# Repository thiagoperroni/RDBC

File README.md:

# RDBC
Radar Didático de Baixo Custo

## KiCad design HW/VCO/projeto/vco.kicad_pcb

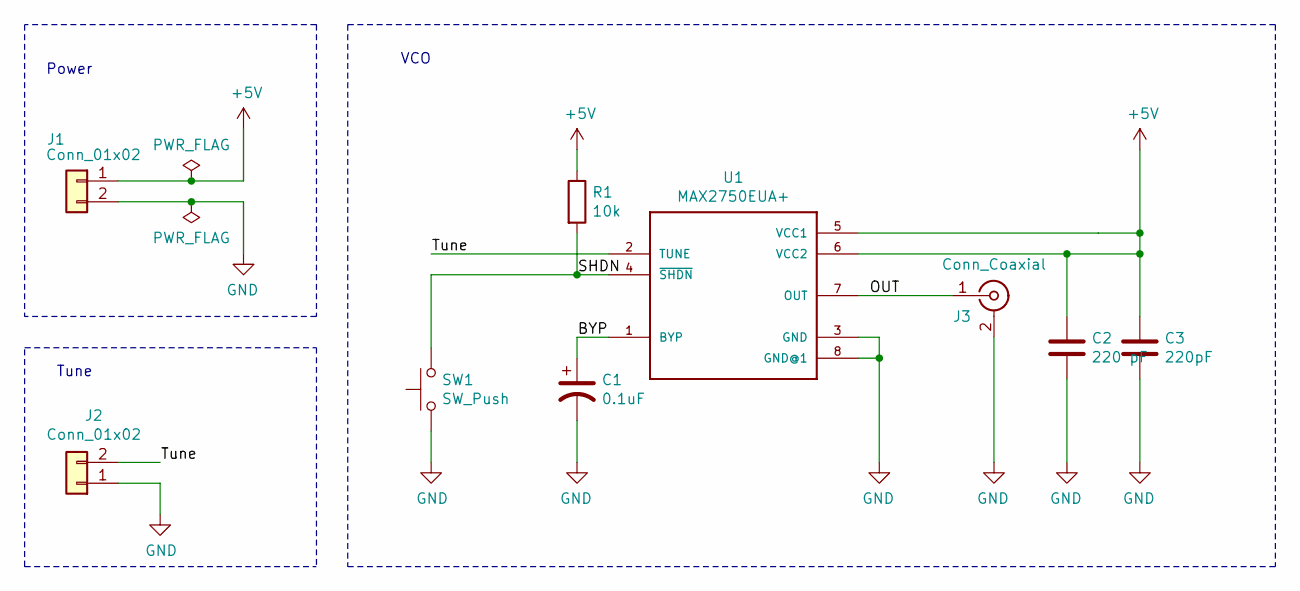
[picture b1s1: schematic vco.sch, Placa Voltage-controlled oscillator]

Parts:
C1: 0.1uF; C_0603_1608Metric
C2: 220 pF; C_0805_2012Metric
C3: 220pF; C_0805_2012Metric
J1, J2: Conn_01x02; PhoenixContact_MSTBVA_2,5_2-G-5,08_1x02_P5.08mm_Vertical
J3: Conn_Coaxial; SMA_Amphenol_901-9215_EdgeMount
R1: 10k; R_1206_3216Metric
SW1: SW_Push; switchRadar
U1: MAX2750EUA+; SOP65P490X110-8N

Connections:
+5V: C2.1, C3.1, J1.1, R1.1, U1.5 (VCC1), U1.6 (VCC2)
/BYP: C1.1, U1.1 (BYP)
/OUT: J3.1 (In), U1.7 (OUT)
/SHDN: R1.2, SW1.2, U1.4 (~SHDN~)
/Tune: J2.2, U1.2 (TUNE)
GND: C1.2, C2.2, C3.2, J1.2, J2.1, J3.2 (Ext), SW1.1, U1.3 (GND), U1.8 (GND@1)

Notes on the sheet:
Power
Tune
VCO

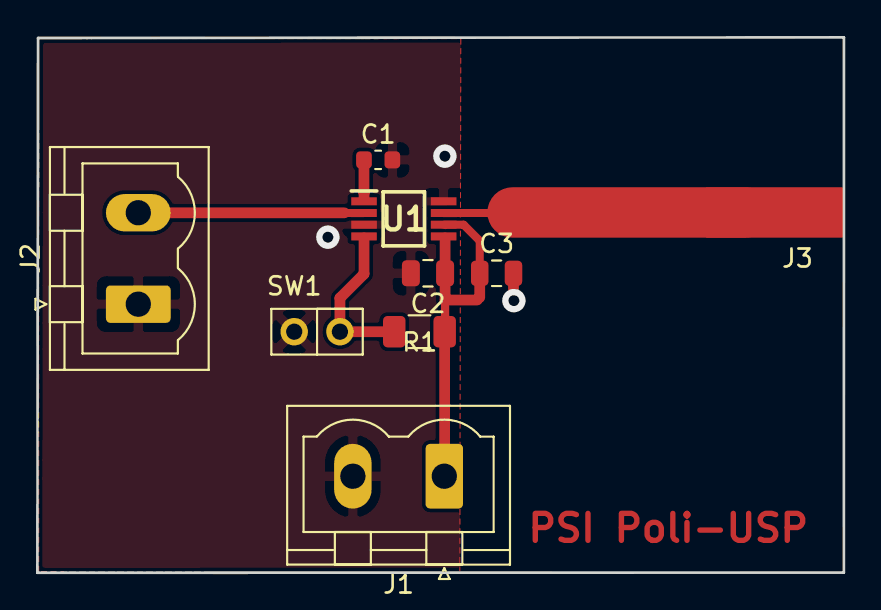
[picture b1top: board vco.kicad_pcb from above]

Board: 2 copper layers, 44.8 x 29.7 mm, 9 parts (0 on the bottom side), 6 nets.

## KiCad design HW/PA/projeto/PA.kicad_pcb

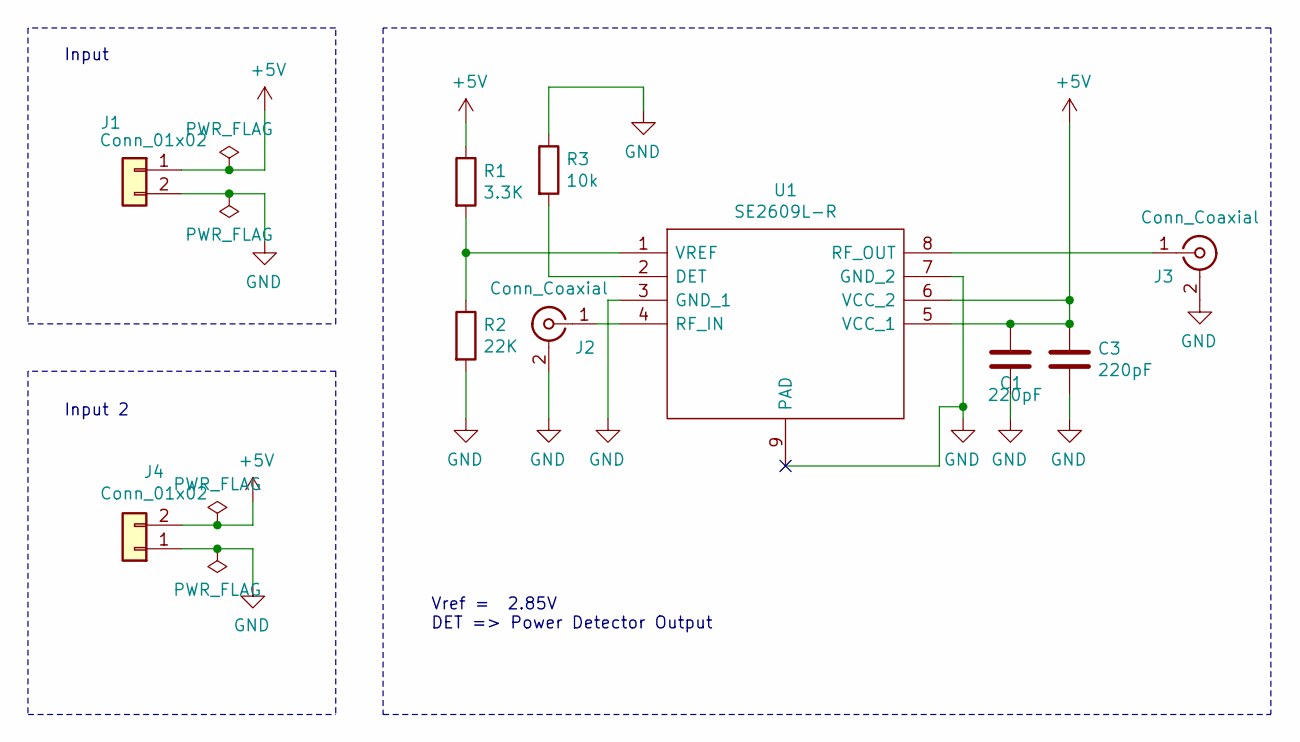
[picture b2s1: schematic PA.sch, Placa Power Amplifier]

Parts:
C1, C3: 220pF; C_0805_2012Metric
J1, J4: Conn_01x02; PhoenixContact_MSTBVA_2,5_2-G-5,08_1x02_P5.08mm_Vertical
J2, J3: Conn_Coaxial; SMA_Amphenol_901-9215_EdgeMount
R1: 3.3K; R_1206_3216Metric
R2: 22K; R_1206_3216Metric
R3: 10k; R_1206_3216Metric
U1: SE2609L-R; QFN-8; Manufacturer_Part_Number SE2609L-R

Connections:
+5V: C1.1, C3.1, J1.1, J4.2, R1.1, U1.5 (VCC_1), U1.6 (VCC_2)
GND: C1.2, C3.2, J1.2, J2.2 (Ext), J3.2 (Ext), J4.1, R2.2, R3.1, U1.3 (GND_1), U1.7 (GND_2), U1.9 (PAD)
unnamed: J2.1 (In), U1.4 (RF_IN)
unnamed: J3.1 (In), U1.8 (RF_OUT)
unnamed: R1.2, R2.1, U1.1 (VREF)
unnamed: R3.2, U1.2 (DET)

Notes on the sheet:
Input
Vref = 2.85V DET => Power Detector Output
Input 2

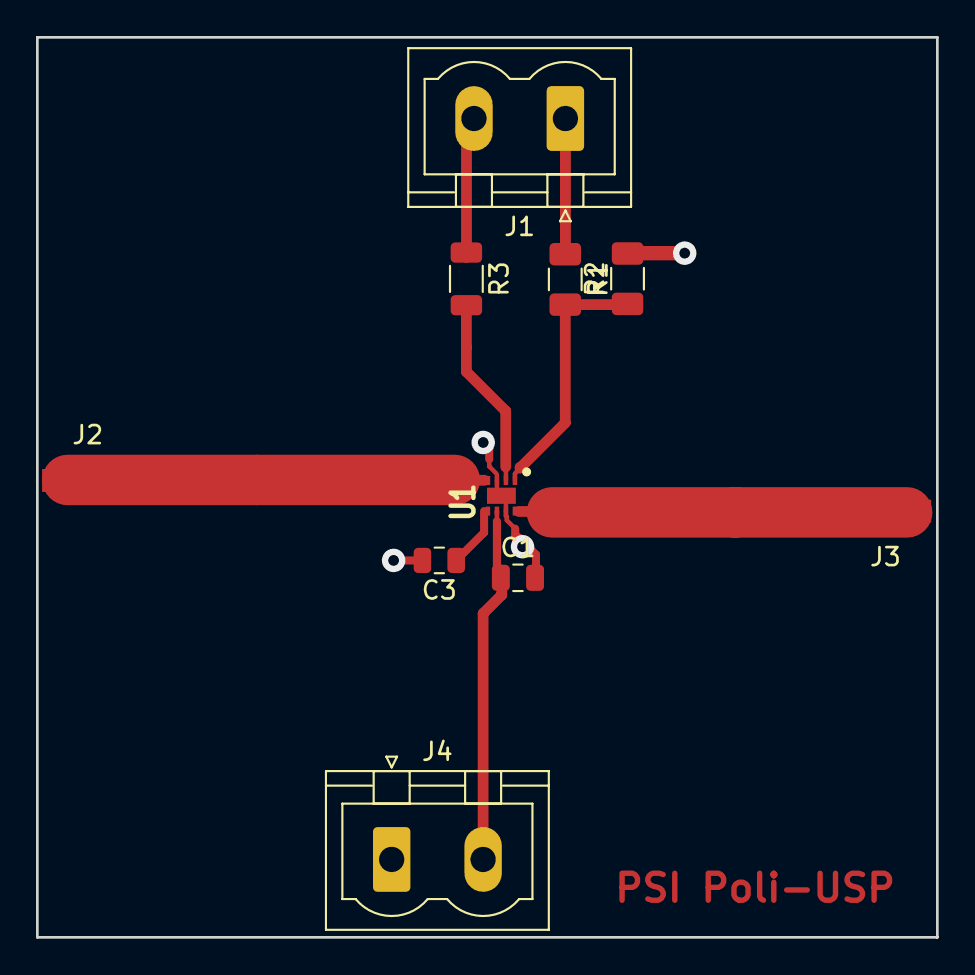
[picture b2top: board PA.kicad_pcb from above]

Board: 2 copper layers, 50.0 x 50.0 mm, 10 parts (0 on the bottom side), 6 nets.

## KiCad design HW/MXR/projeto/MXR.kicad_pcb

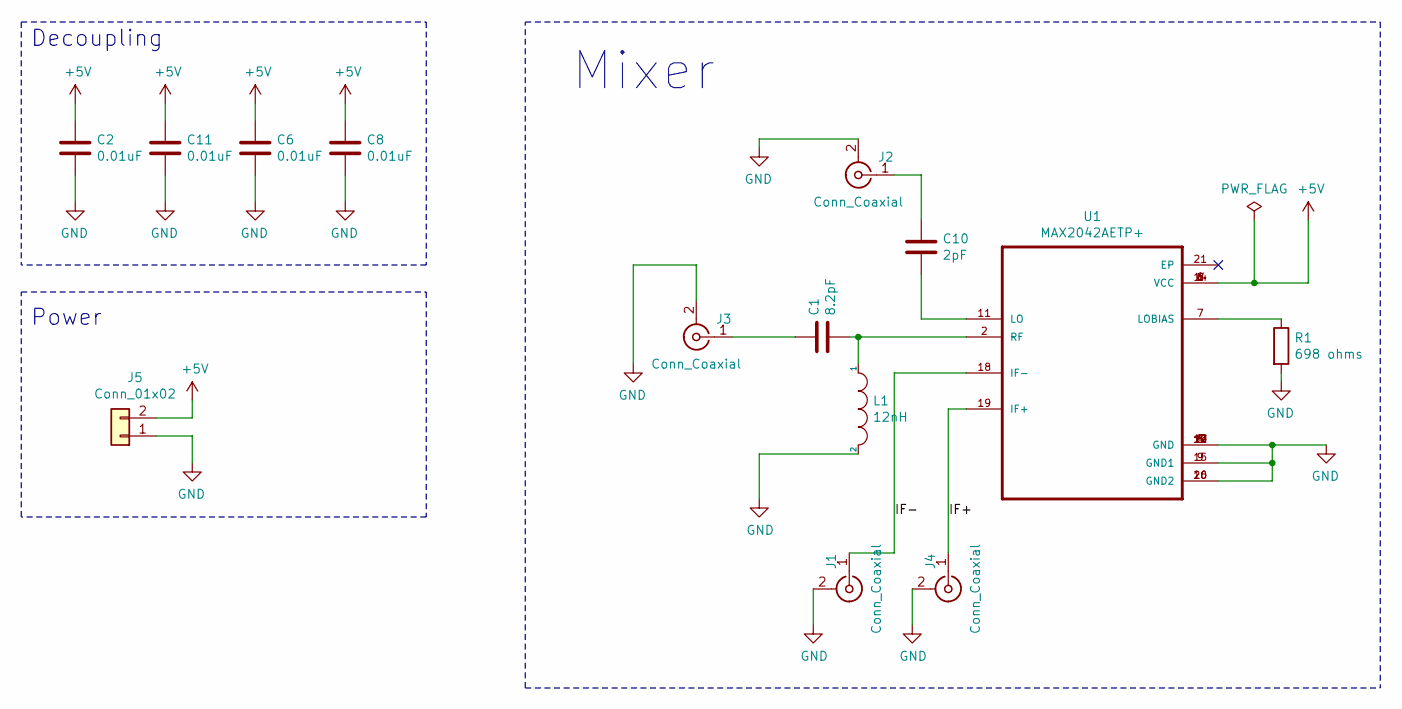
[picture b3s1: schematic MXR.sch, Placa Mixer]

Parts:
C1: 8.2pF; C_0402_1005Metric
C2, C6, C8, C11: 0.01uF; C_0402_1005Metric
C10: 2pF; CAPC1005X55N
J1, J4: Conn_Coaxial; BNC_TEConnectivity_1478204_Vertical
J2, J3: Conn_Coaxial; SMA_Amphenol_901-9215_EdgeMount
J5: Conn_01x02; PhoenixContact_MSTBVA_2,5_2-G-5,08_1x02_P5.08mm_Vertical
L1: 12nH; L_0402_1005Metric
R1: 698 ohms; R_0402_1005Metric
U1: MAX2042AETP+; TQFN-20-1EP_5x5mm_P0.65mm_EP3.1x3.1mm

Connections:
+5V: C2.1, C6.1, C8.1, C11.1, J5.2, U1.1 (VCC), U1.6 (VCC), U1.8 (VCC), U1.14 (VCC)
/IF+: J4.1 (In), U1.19 (IF+)
/IF-: J1.1 (In), U1.18 (IF-)
GND: C2.2, C6.2, C8.2, C11.2, J1.2 (Ext), J2.2 (Ext), J3.2 (Ext), J4.2 (Ext), J5.1, L1.2, R1.2, U1.3 (GND), U1.4 (GND), U1.5 (GND), U1.9 (GND1), U1.10 (GND), U1.12 (GND), U1.13 (GND), U1.15 (GND1), U1.16 (GND2), U1.17 (GND), U1.20 (GND2)
unnamed: C1.1, J3.1 (In)
unnamed: C1.2, L1.1, U1.2 (RF)
unnamed: C10.1, J2.1 (In)
unnamed: C10.2, U1.11 (LO)
unnamed: R1.1, U1.7 (LOBIAS)

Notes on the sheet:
Mixer
Decoupling
Power

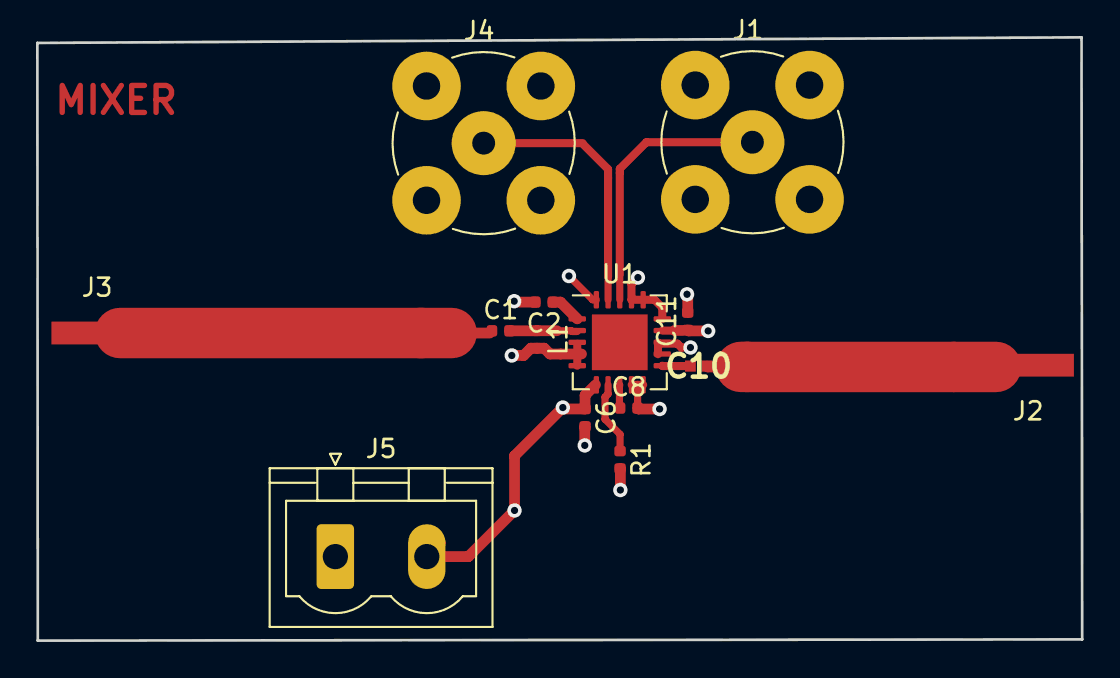
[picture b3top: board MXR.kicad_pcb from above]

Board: 2 copper layers, 58.0 x 33.5 mm, 14 parts (0 on the bottom side), 9 nets.

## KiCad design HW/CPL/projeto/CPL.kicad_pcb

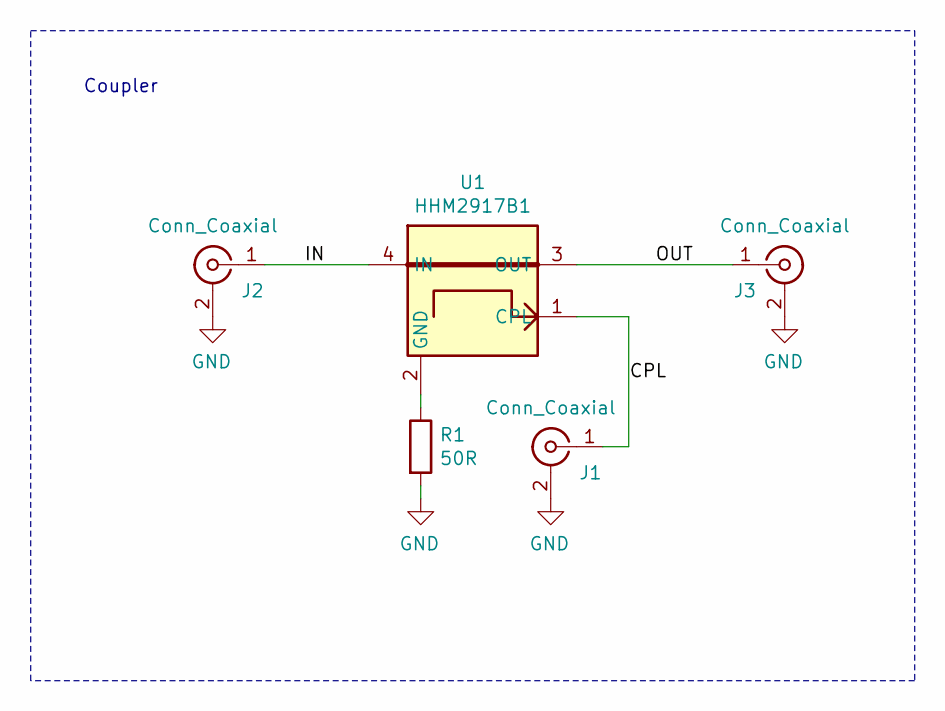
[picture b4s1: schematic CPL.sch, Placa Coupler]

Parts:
J1, J2, J3: Conn_Coaxial; SMA_Amphenol_901-9215_EdgeMount
R1: 50R; R_1206_3216Metric
U1: HHM2917B1; CPL-0402

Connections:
/CPL: J1.1 (In), U1.1 (CPL)
/IN: J2.1 (In), U1.4 (IN)
/OUT: J3.1 (In), U1.3 (OUT)
GND: J1.2 (Ext), J2.2 (Ext), J3.2 (Ext), R1.2
unnamed: R1.1, U1.2 (GND)

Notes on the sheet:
Coupler

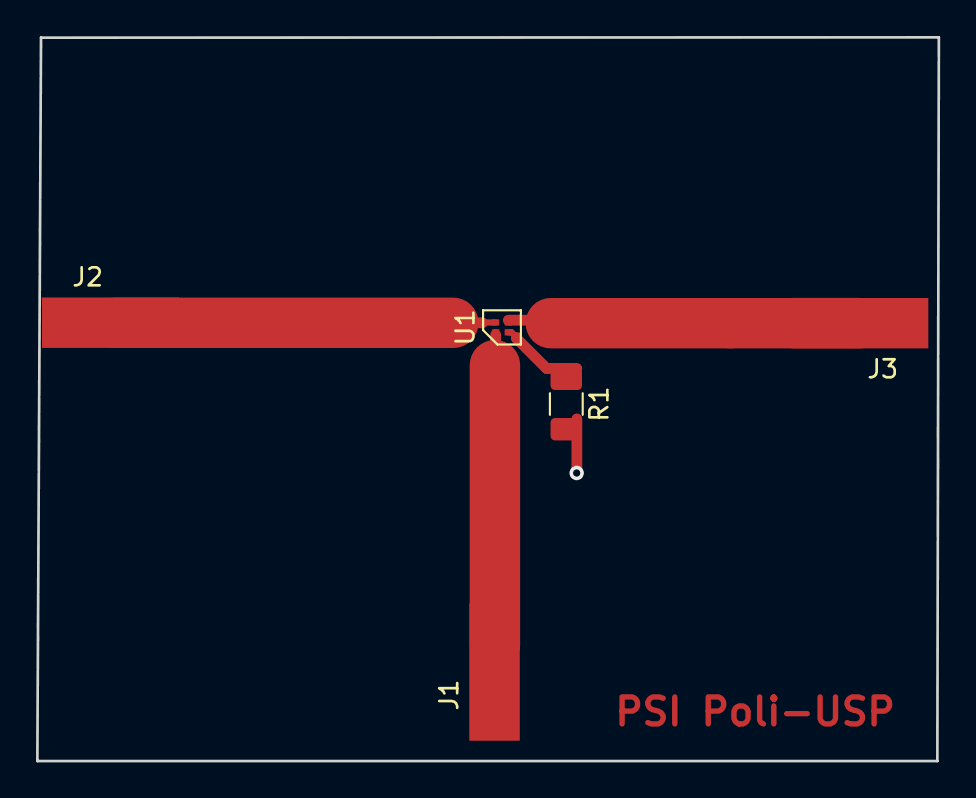
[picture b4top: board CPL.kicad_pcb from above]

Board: 2 copper layers, 50.1 x 40.2 mm, 5 parts (0 on the bottom side), 5 nets.

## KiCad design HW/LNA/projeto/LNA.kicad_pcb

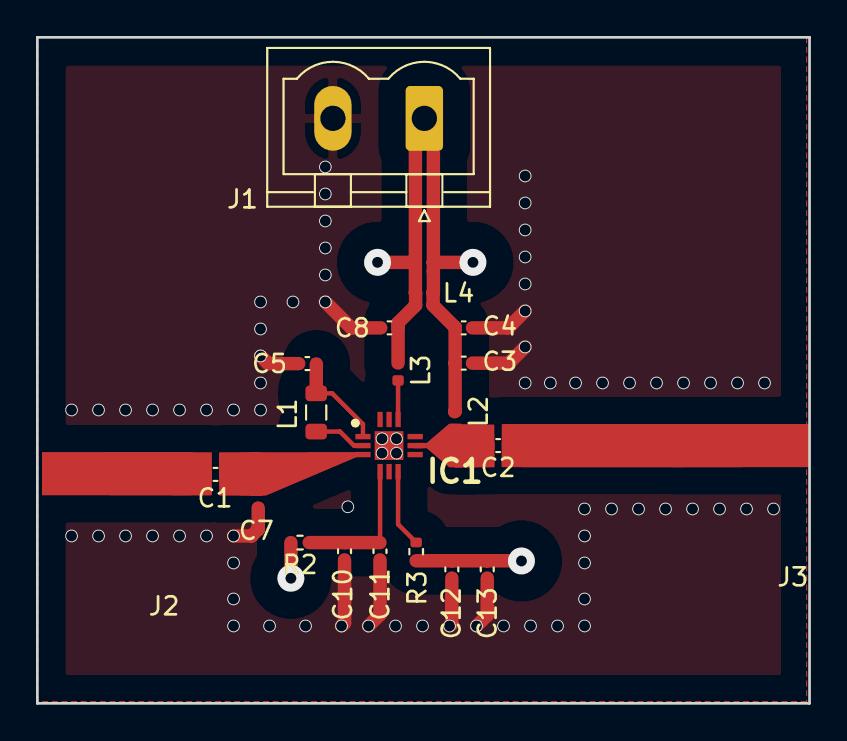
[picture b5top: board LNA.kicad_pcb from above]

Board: 2 copper layers, 42.9 x 37.0 mm, 21 parts (0 on the bottom side), 11 nets.

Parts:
C1, C2, C3, C4, C5, C7, C8, C10, C11, C12, C13: C; C_0402_1005Metric
IC1: MML20242HT1; QFN50P300X300X90-13N-D
J1: Conn_01x02; PhoenixContact_MSTBVA_2,5_2-G-5,08_1x02_P5.08mm_Vertical
J2, J3: Conn_Coaxial; SMA_Amphenol_901-9215_EdgeMount
L1: L; L_0805_2012Metric
L2, L3, L4: L; L_0402_1005Metric
R2, R3: R; R_0402_1005Metric

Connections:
+5V: C3.1, C4.1, C8.1, C12.2, C13.2, J1.1, L2.1, L3.1, L4.1, L4.2, R2.2, R3.1
/RF_in_2: C1.2, C7.2, IC1.3
GND: C3.2, C4.2, C5.2, C7.1, C8.2, C10.1, C11.1, C12.1, C13.1, IC1.13, J1.2, J2.2, J3.2
unnamed: C1.1, J2.1
unnamed: C2.1, IC1.8, L2.2
unnamed: C2.2, J3.1
unnamed: C5.1, IC1.1, L1.1
unnamed: C10.2, C11.2, IC1.4, R2.1
unnamed: IC1.2, L1.2
unnamed: IC1.6, R3.2
unnamed: IC1.10, L3.2

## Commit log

2021-09-15 Added project files for hardware
    Initial files for HW project on Kicad
2021-09-15 Added project files for software
    Initial files for SW project on STM32CubeIDE
2022-01-24 SW: Added ADC acquisition and UART communication
2022-01-24 Added LabView VI
2022-01-29 Added Coupler PCB
2022-01-29 Added Mixer PCB
2022-01-29 Added LNA PCB
2022-01-29 Added PA PCB
2022-01-29 Added VCO PCB
